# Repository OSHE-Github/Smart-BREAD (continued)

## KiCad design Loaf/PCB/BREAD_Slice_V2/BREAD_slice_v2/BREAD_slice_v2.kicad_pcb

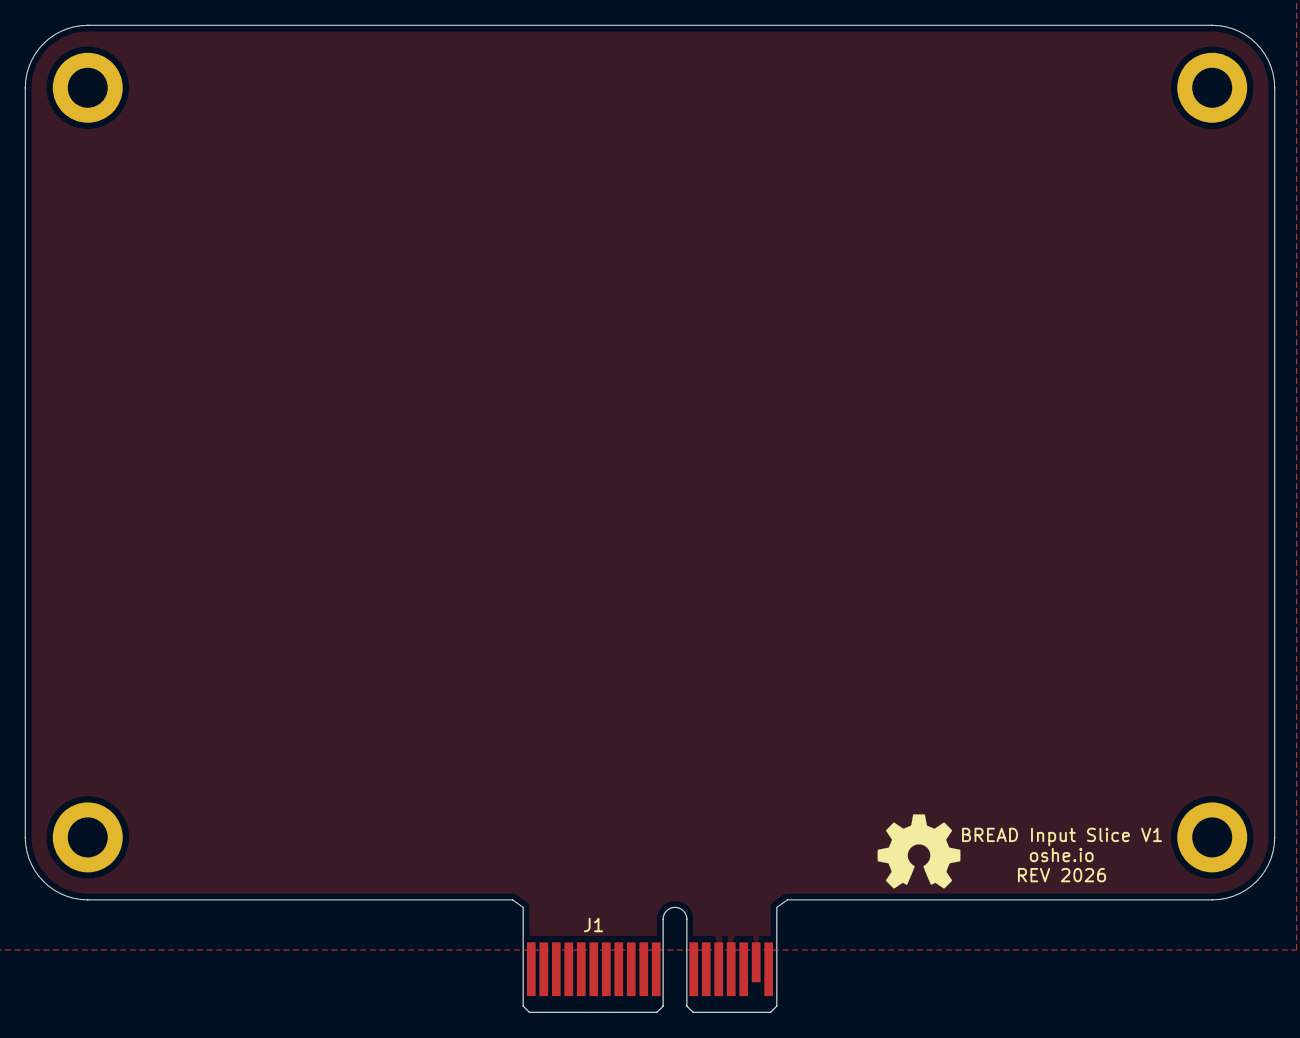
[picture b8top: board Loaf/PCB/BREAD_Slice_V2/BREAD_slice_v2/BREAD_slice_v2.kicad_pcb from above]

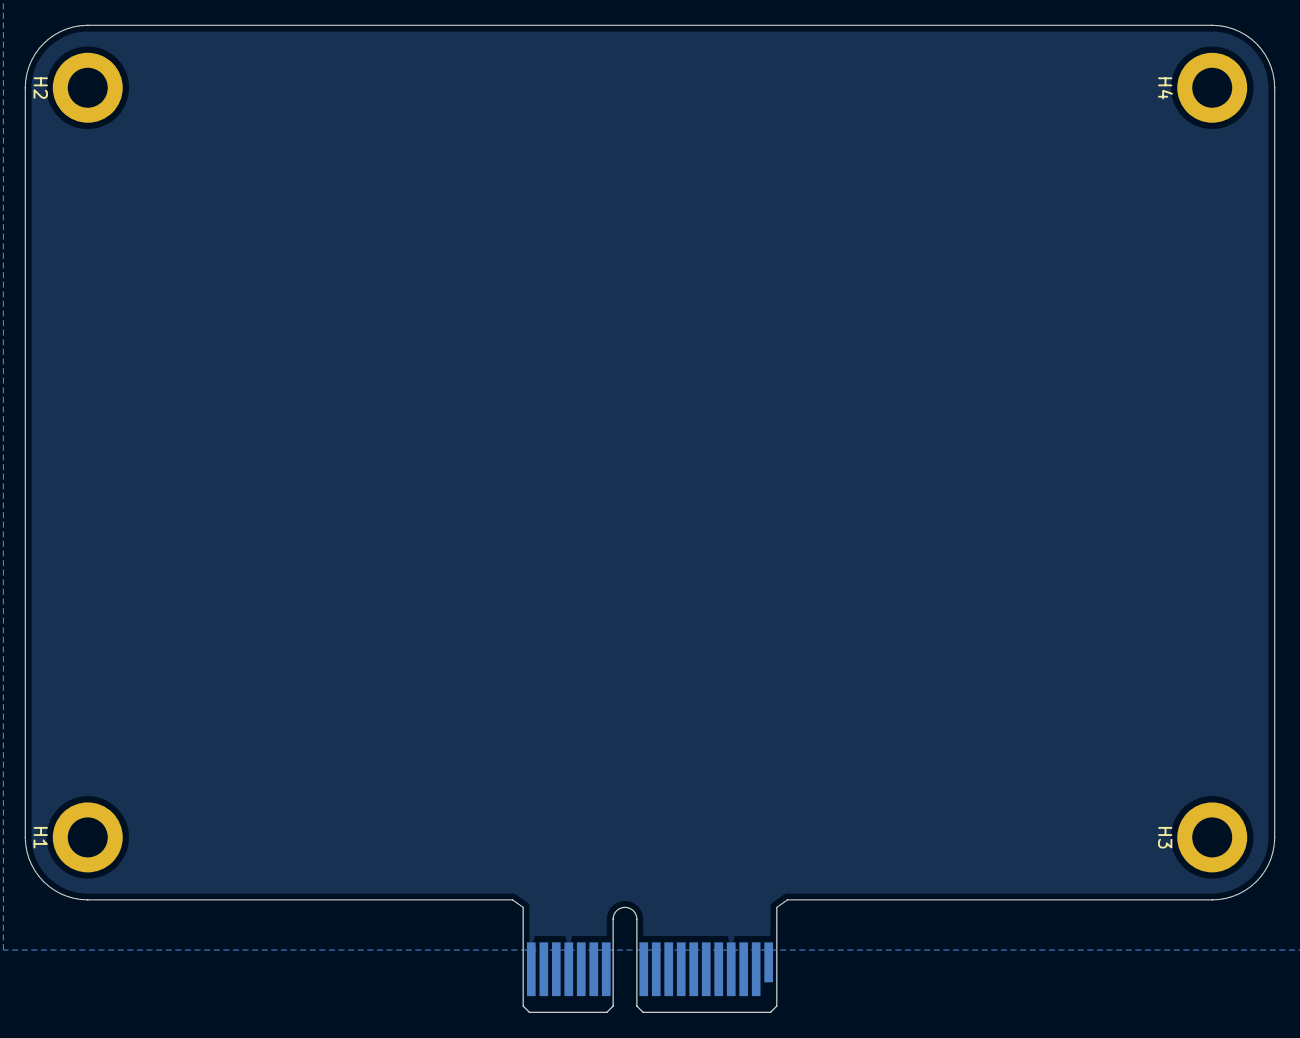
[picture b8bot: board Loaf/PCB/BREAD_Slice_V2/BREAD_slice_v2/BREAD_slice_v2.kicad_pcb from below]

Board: 2 copper layers, 100.0 x 79.0 mm, 6 parts (4 on the bottom side), 3 nets, no tracks yet.

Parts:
H1, H2, H3, H4: MountingHole; MountingHole_3.2mm_M3_DIN965_Pad
J1: 10018783-10200TLF; BUS_PCIexpress_x1
Logo1: Logo_Open_Hardware_Small; OSHW-Symbol_6.7x6mm_SilkScreen

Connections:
+5V: J1.A13, J1.A14, J1.B14, J1.B15, J1.B17
+12V: J1.A1, J1.A2, J1.A3, J1.B1, J1.B2, J1.B3
GND: J1.A4, J1.A15, J1.A18, J1.B4, J1.B7, J1.B16, J1.B18

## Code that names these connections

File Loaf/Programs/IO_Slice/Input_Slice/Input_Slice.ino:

#include <SPI.h>
#include <ACAN2515.h>
#include "MCP3208.h"

//CAN Configuration
#define CANCS   1
#define CANINT  4
#define canTXID 0x100
#define canRXID 0x1A3
#define OSCFREQ 16000000 // 16 MHz
#define CANSPEED 500000 // 500 kbps

//CAN Setup
ACAN2515 can(CANCS, SPI, CANINT);
CANMessage txMSG;
CANMessage rxMSG;
CANMessage EMSG;
CANMessage workMSG;

//Can Frame Vars
uint8_t dataLen = 8;
int16_t canID = 0;

//CAN Buffers
#define bufSize 16
CANMessage txBuffer[bufSize];
CANMessage rxBuffer[bufSize];
char txFlagBuf[bufSize];
char rxFlagBuf[bufSize];

//Decoded value vars
uint8_t modeIO = 0;
uint8_t modeFlag = 0 ;
uint8_t pinNum = 0;
uint8_t res1 = 0;
uint8_t res2 = 0;
int16_t bulkDigi = 0;
uint8_t pwmDuty = 0;
int32_t dataSeg = 0;

//Counters
uint32_t lastMessageTime = 0;
uint32_t messageCounter = 0;

//Core vars
volatile char core0Setup = 0;
volatile char core1Setup = 0;
volatile char STOPTHISMADNESS = 0;

//ADC Configuration
#define ADCCS 7
#define numAnalog 8
MCP3208 externADC;

//Digital pin setup
#define ESTOP 5
#define numDigital 8
const uint8_t digiPins[numDigital] {26, 22, 21, 20, 19, 18, 17, 16}; //DIO0, DIO1, DIO2, DIO3, DIO4, DIO5, DIO6, DIO7

//Runtime Flags
#define canDebug false

//Decode the CAN message recieved into the required fields. Refer to I/O Slice CAN message spec for details.
void canDecode(uint8_t canData[]){
  char byte = canData[0];
  modeIO = (byte & 0b11000000) >> 6;
  modeFlag =  (byte & 0b00110000) >> 4;
  pinNum =  byte & 0b00001111;

  //Reserved data reading
  //res1 = canMsg.data[1];

  //PWM Duty cycle reading
  if(modeFlag == 2){pwmDuty = canData[4];}

  //Bulk Digital pin decoding
  if(modeFlag == 3){
    bulkDigi = canData[2];
    bulkDigi = (bulkDigi << 8) + canData[3];
  }

  //Data Segment Decoding
  dataSeg = canData[5];
  dataSeg = (dataSeg << 8) + canData[6];
  dataSeg = (dataSeg << 8) + canData[7];
}

//Encode a new message and return the encoded message
CANMessage canEncode(uint16_t bulkDigi, uint8_t pwmDuty, uint32_t dataSeg){
  CANMessage out;

  out.id = canTXID;
  out.len = dataLen;

  //Info Byte encoding
  out.data[0] = 0b10000000;
  out.data[0] = out.data[0] + pinNum + (modeFlag << 4);

  //Reserved bits encoding
  out.data[1] = 0; out.data[4] = 0;

  //Bulk digital data encoding
  out.data[2] = char(bulkDigi >> 8);
  out.data[3] = char(bulkDigi & 0b0000000011111111);

  //Data segment encoding
  out.data[5] = char(dataSeg >> 16);
  out.data[6] = char(dataSeg >> 8) & 0b000000000000000011111111;
  out.data[7] = char(dataSeg & 0b000000000000000011111111);

  //Encode PWM duty cycle
  out.data[4] = pwmDuty;

  return out;
}

uint16_t readAnalog(uint8_t pin){
  uint16_t out = 0;
  Serial.print("Reading analog pin: "); Serial.println(digiPins[pin]);
  out = externADC.analogRead(pin);
  Serial.print(out); Serial.println(" Counts");

  float voltage = (out * 3.3) / 4095.0;
  Serial.print(voltage); Serial.println(" V");

  return out;
}

//Read specified digital pin
uint16_t readDigital(uint8_t pin){
  uint16_t out = 0;
  out = digitalRead(digiPins[pin]);
  //Serial.print("Read digital pin: ");
  //Serial.println(digiPins[pin]);
  //Serial.println(out);
  return out;
}

//Read many digital pins
uint16_t readManyDigital(uint16_t pins){
  uint16_t out = 0;
  for(uint16_t i = 0; i < numDigital; i++){
    //Mask pins so that we can efficiently calculate if the pin is to be read or not.
    uint16_t mask = 0b0000000000000000 + (1 << i);
    uint16_t flag = pins & mask;

    //Read and add result to output.
    if(mask > 0){
      out = out + (digitalRead(digiPins[i]) << i);
    }
  }
  Serial.print("Read from all digital pins: "); Serial.println(out, BIN);
  return out;
}

void readPWM(uint8_t pin){
  //Listen for pwm signal
  unsigned long highTime = pulseIn(digiPins[pin], HIGH);
  unsigned long lowTime = pulseIn(digiPins[pin], LOW);
  float freq = 0;
  float duty = 0;

  if (highTime + lowTime > 0) {
    unsigned long period = highTime + lowTime;
    freq = 1000000.0 / period;
    duty = ((float)highTime / period) * 100.0;

    Serial.print("Freq: ");
    Serial.print(freq);
    Serial.print(" Hz | Duty Cycle: ");
    Serial.print(duty);
    Serial.println(" %");
  } else {
    Serial.println("No PWM signal present");
    freq = 0;
    duty = 0;
  }

  pwmDuty = uint8_t(255 * (duty/100.0));
  dataSeg = freq;
}

void setup() {
  //Serial monitor init
  Serial.begin(115200);
  while(!Serial){}

  //SPI Config
  SPI.setRX(0);
  SPI.setSCK(2);
  SPI.setTX(3);
  SPI.begin();

  ACAN2515Settings settings(OSCFREQ, CANSPEED);
  externADC.begin(ADCCS);
  externADC.analogReadResolution(12);

  Serial.println("Initializing MCP2515...");
  const uint32_t initErrorCode = can.begin(settings, [] { can.isr(); });

  if (initErrorCode == 0) {
    Serial.println("MCP2515 Initialized Successfully!");
  } else {
    Serial.print("Initialization failed. Error code: 0x");
    Serial.println(initErrorCode, HEX);
    while (1);
  }

  //Capture to make sure the cores don't progress too out of sync
  core0Setup = 1;
  while(!core1Setup){}
}

void setup1(){
  pinMode(ESTOP, INPUT);

  for(char i = 0; i < numDigital; i++){
    pinMode(digiPins[i], INPUT);
  }

  //Format flag buffers
  for(char i = 0; i < bufSize; i++){
    txFlagBuf[i] = 0;
    rxFlagBuf[i] = 0;
  }

  EMSG.id = 0x0;
  EMSG.len = 8;

  for(char i = 0; i < 8; i++){
    EMSG.data[i] = 0b11111111;
  }


  //Capture to make sure the cores don't progress too out of sync
  core1Setup = 1;
  while(!core0Setup){}
}

void loop() {
  while(true){
  while(STOPTHISMADNESS){
    can.tryToSend(EMSG);
    Serial.println("ESTOP TRIGGERED!!!!!!!!!");
    delay(100);
  }
  //Recieve the CAN message
  if (can.available()) {
    can.receive(rxMSG);
    //Yoink ID and data size
    canID = rxMSG.id;
    dataLen = rxMSG.len;
    Serial.println("]");

    //Skip this frame if it isn't what we want
    if(canID != canRXID && dataLen != 8){continue;}

    //Print CAN Frame
    //Serial.println("Sending CAN Message");
    Serial.print("RX Data: [");
    for(char i = 0; i < 7; i++){
      Serial.print(rxMSG.data[i], BIN);
      Serial.print(", ");
    }
    Serial.print(rxMSG.data[7], BIN);
    Serial.println("]");

    //Search for free space in the buffer
    for(char i = 0; i < bufSize; i++){
      if(rxFlagBuf[i] == 0){
        rxFlagBuf[i] = 1;
        rxBuffer[i] = rxMSG;  
        break;
      }
    }
  }

  //Search for any CAN messages to send in buffer
  for(char i = 0; i < bufSize; i++){

    //Send any unsent messages
    if(txFlagBuf[i] == 1){
      txMSG = txBuffer[i];
      //Print CAN Frame
      //Serial.println("Sending CAN Message");
      Serial.print("Data: [");
      for(char i = 0; i < 7; i++){
        Serial.print(txMSG.data[i], BIN);
        Serial.print(", ");
      }
      Serial.print(txMSG.data[7], BIN);
      Serial.println("]");

      //Send message
      char ok = can.tryToSend(txMSG);

      //Keep trying if there was a failure
      while(!ok){
        ok = can.tryToSend(txMSG);
      }

      //Set flag to 0 to mark it as free space
      txFlagBuf[i] = 0;
    }
  }
}}

void loop1(){
  while(true){
  STOPTHISMADNESS = digitalRead(ESTOP);
  while(STOPTHISMADNESS){}

  for(char i = 0; i < bufSize; i++){

    //Check if the buffer entry is ready
    if(rxFlagBuf[i] == 1){

      //Decode buffer entry
      canDecode(rxBuffer[i].data);

      if(modeIO == 0){
        //Read stuff
        switch(modeFlag){
            //Analog Case
            case 0:
            break;

            //Digital Case
            case 1:
            break;

            //Bulk Digital Case
            case 2:
            break;

            //PWM Case
            case 3:
            break;
          }
        txBuffer[i] = canEncode(bulkDigi, pwmDuty, dataSeg);
        txFlagBuf[i] = 1;
        rxFlagBuf[i] = 0;
      }else{
        rxFlagBuf[i] = 0;
      }
    }
  }
  
}}
